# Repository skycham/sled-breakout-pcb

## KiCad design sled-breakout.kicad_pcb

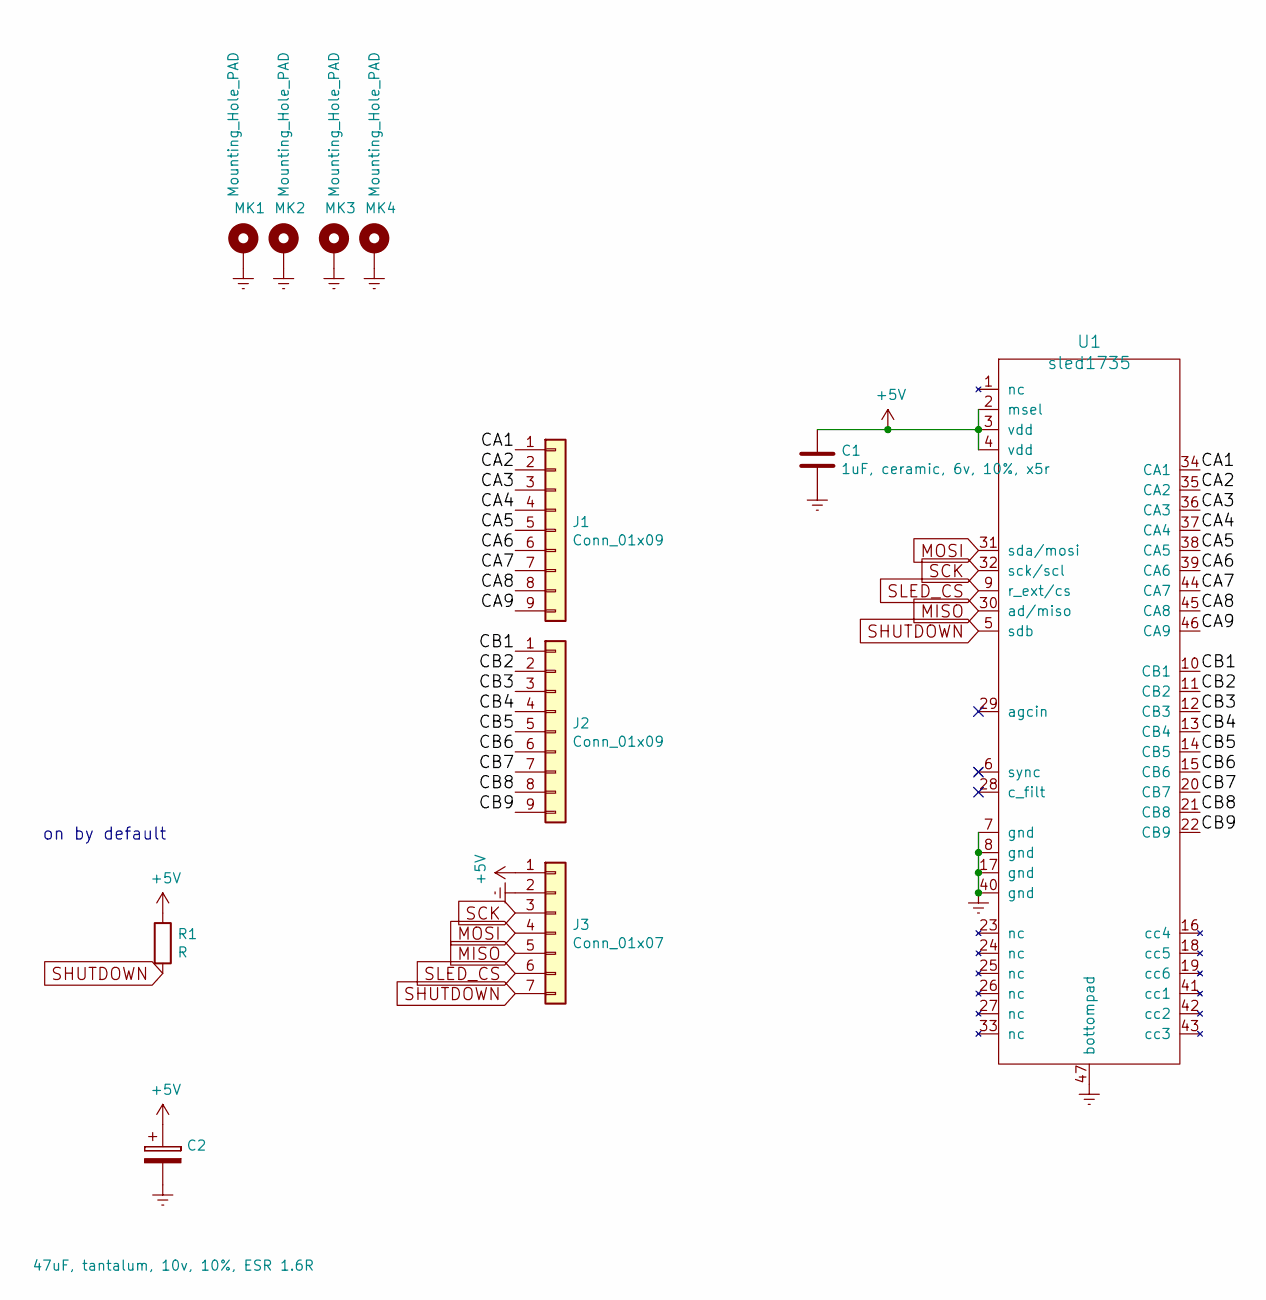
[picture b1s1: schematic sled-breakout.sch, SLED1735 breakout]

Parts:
C1: 1uF, ceramic, 6v, 10%, x5r; C_0603; farnell # 1865556
C2: 47uF, tantalum, 10v, 10%, ESR 1.6R; CP_EIA-3528-21_Kemet-B; farnell # 1432366
J1, J2: Conn_01x09; Pin_Header_Straight_1x09_Pitch2.54mm
J3: Conn_01x07; Pin_Header_Straight_1x07_Pitch2.54mm
MK1, MK2, MK3, MK4: Mounting_Hole_PAD; MountingHole_3.2mm_M3_DIN965_Pad
R1: R; R_0603
U1: sled1735; QFN-46_EP_4.5x6.5_Pitch0.4mm

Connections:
+5V: C1.1, C2.1, J3.1, R1.1, U1.2 (msel), U1.3 (vdd), U1.4 (vdd)
/CA1: J1.1, U1.34 (CA1)
/CA2: J1.2, U1.35 (CA2)
/CA3: J1.3, U1.36 (CA3)
/CA4: J1.4, U1.37 (CA4)
/CA5: J1.5, U1.38 (CA5)
/CA6: J1.6, U1.39 (CA6)
/CA7: J1.7, U1.44 (CA7)
/CA8: J1.8, U1.45 (CA8)
/CA9: J1.9, U1.46 (CA9)
/CB1: J2.1, U1.10 (CB1)
/CB2: J2.2, U1.11 (CB2)
/CB3: J2.3, U1.12 (CB3)
/CB4: J2.4, U1.13 (CB4)
/CB5: J2.5, U1.14 (CB5)
/CB6: J2.6, U1.15 (CB6)
/CB7: J2.7, U1.20 (CB7)
/CB8: J2.8, U1.21 (CB8)
/CB9: J2.9, U1.22 (CB9)
Earth: C1.2, C2.2, J3.2, MK1.1, MK2.1, MK3.1, MK4.1, U1.7 (gnd), U1.8 (gnd), U1.17 (gnd), U1.40 (gnd), U1.47 (bottompad)
MISO: J3.5, U1.30 (ad/miso)
MOSI: J3.4, U1.31 (sda/mosi)
SCK: J3.3, U1.32 (sck/scl)
SHUTDOWN: J3.7, R1.2, U1.5 (sdb)
SLED_CS: J3.6, U1.9 (r_ext/cs)

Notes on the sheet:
on by default

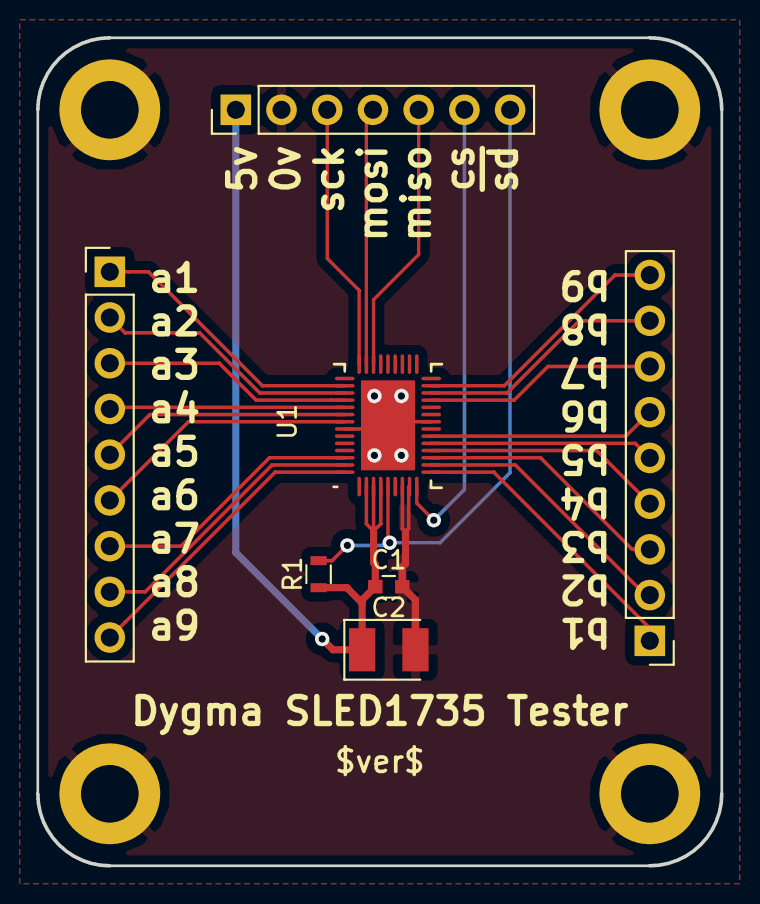
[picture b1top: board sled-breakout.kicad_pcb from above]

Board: 2 copper layers, 38.0 x 46.0 mm, 11 parts (0 on the bottom side), 25 nets.

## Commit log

2018-11-28 removed old trace
2018-12-05 B header was labelled upside down
